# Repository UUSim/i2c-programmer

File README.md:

# Handheld i2c bus programmer (with real time clock)
This repository hosts the Kicad-based design for a handheld i2c bus programmer/scanner with real time clock. The device features:
- DC power (rated 7-12V)
- Powered via i2c bus connector (TBD)
- LCD user interface
- Input via rotary encoder with switch
- It's own clock (on separate i2c bus) + battery backup
- Configurable i2c pullup resistors
- Square wave signal of DS1307 accessible via header

Functions:
- Scan for devices on i2c bus
- Debug i2c protocol
- Set/Read time of internal RTC
- Set/Read time RTC on external i2c bus
- Expose own RTC to external i2c bus
- Communicate with i2c devices on bus

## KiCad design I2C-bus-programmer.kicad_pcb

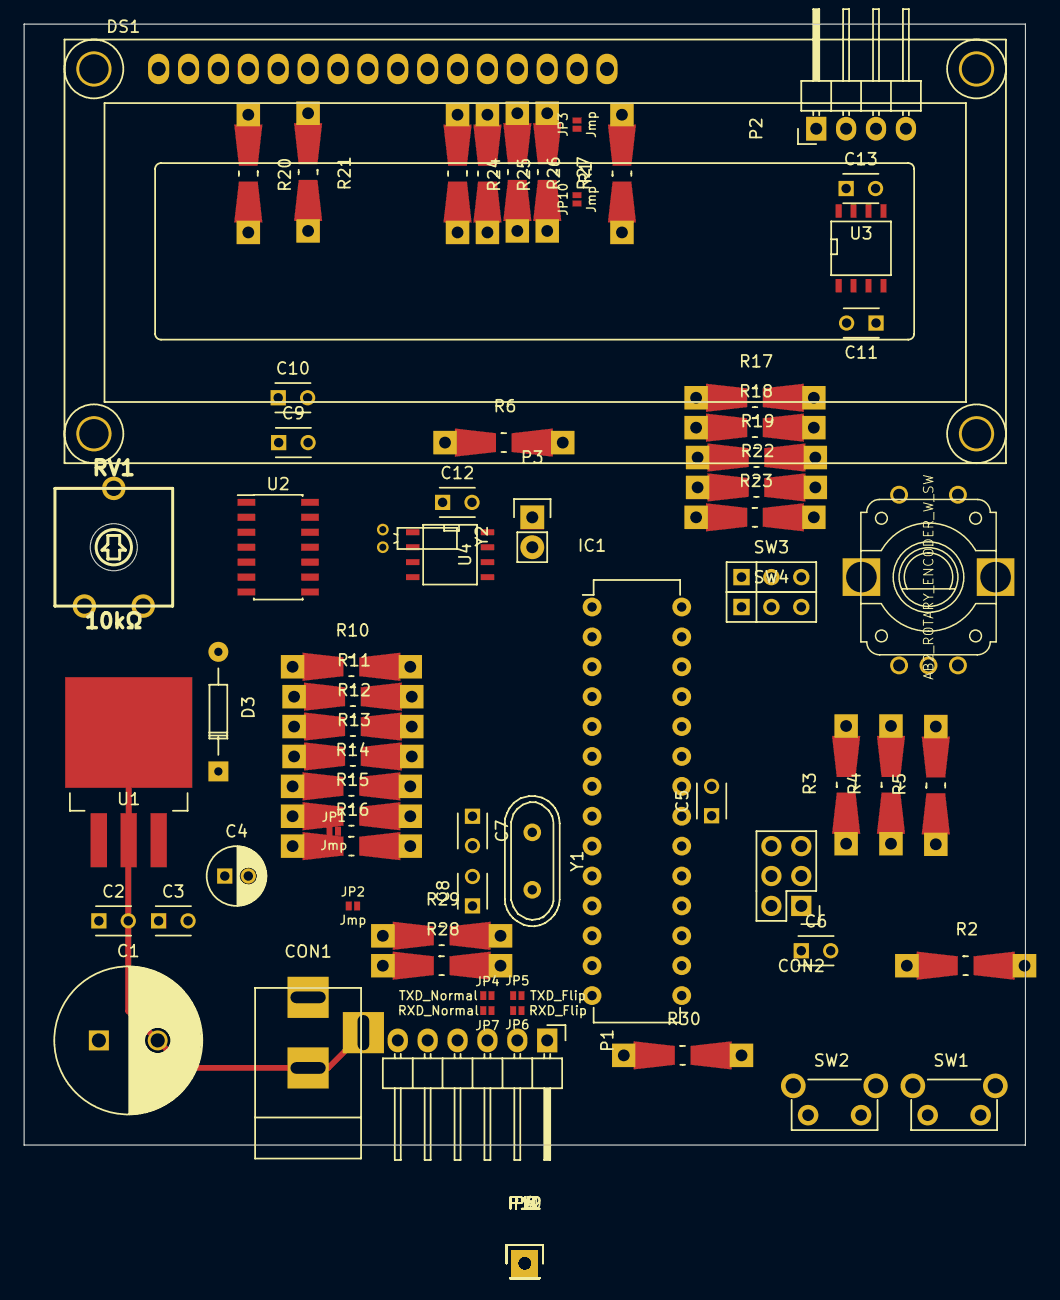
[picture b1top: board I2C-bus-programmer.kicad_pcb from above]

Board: 2 copper layers, 85.1 x 95.2 mm, 77 parts (0 on the bottom side), 61 nets.

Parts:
C1: 2200μF; C_Radial_D12.5_L25_P5
C2, C3, C5, C9, C12: 0.1μF; C_Disc_D3_P2.5
C4: 10μF; C_Radial_D5_L11_P2
C6: 100nF; C_Disc_D3_P2.5
C7, C8: 22pF; C_Disc_D3_P2.5
C10, C11, C13: 1μF; C_Disc_D3_P2.5
CON1: BARREL_JACK
CON2: AVR-ISP-6; Pin_Header_Straight_2x03
D3: 1N4148; Diode_DO-35_SOD27_Horizontal_RM10
DS1: LCD16X2; WC1602A
IC1: ATMEGA328P-P; DIP-28_W7.62mm
JP1, JP2, JP3, JP10: Jmp; S_JUMPER_2
JP4: TXD_Normal; S_JUMPER_2
JP5: TXD_Flip; S_JUMPER_2
JP6: RXD_Flip; S_JUMPER_2
JP7: RXD_Normal; S_JUMPER_2
P1: FTDI_Header; Pin_Header_Angled_1x06
P2: I2C_Header; Pin_Header_Angled_1x04
P3: CONN_01X02; Pin_Header_Straight_1x02
P4, P5, P6, P7, P8, P9, P10, P11, P12: CONN_01X01; Pin_Header_Straight_1x01
R1: 220Ω; Resistor_SMD+THTuniversal_0805to1206_RM10_HandSoldering
R2, R3, R4, R5, R6, R10, R11, R12, R13, R30: 10kΩ; Resistor_SMD+THTuniversal_0805to1206_RM10_HandSoldering
R14, R15, R16, R17, R18, R19, R22, R23: 4.7kΩ; Resistor_SMD+THTuniversal_0805to1206_RM10_HandSoldering
R20, R21, R24, R25, R26, R27, R28, R29: 100Ω; Resistor_SMD+THTuniversal_0805to1206_RM10_HandSoldering
ROT_ENC1: AB2_ROTARY_ENCODER_W_SW; AB2_ROTARY_ENCODER_W_SWITCH
RV1: 10kΩ; trimmer_ecp_ca9-v10
SW1, SW2: SW_Push; SW_Tactile_SPST_Angled
SW3, SW4: SW_SPDT; SW_Micro_SPST
U1: LM7805CT; TO-263-3Lead
U2: PCA9543; SOIC-14_3.9x8.7mm_Pitch1.27mm
U3: ISO1540; SOIC-8-N
U4: DS1307Z+; SOIC-8-N
Y1: 16MHz; Crystal_HC49-U_Vertical
Y2: 32.768kHz; Crystal_Round_Horizontal_2mm

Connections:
+5V: C9.1, C10.1, C11.2, C12.2, CON2.2, DS1.2, IC1.7, IC1.20, JP2.2, JP3.2, P1.4, P11.1, R1.2, R2.1, R3.1, R4.1, R5.1, R6.1, R10.2, R11.2, R12.2, R13.2, R14.1, R15.1, R16.1, R17.1, R18.1, R19.1, R30.1, RV1.1, U2.14, U3.1, U4.8
+12V: C1.1, C2.1, CON1.1, D3.1, U1.1
/DTR: C6.2, P1.1
/RXI: JP5.2, JP7.2, P1.3
/TXO: JP4.2, JP6.2, P1.2
Button1: IC1.26, SW2.1
CLK: CON2.3, IC1.19, R27.2
GNDA: C5.2, C7.2, C8.2, C9.2, C10.2, C11.1, C12.1, CON2.6, DS1.1, DS1.5, DS1.16, IC1.8, IC1.22, JP1.2, P1.5, P1.6, P3.2, P12.1, R30.2, ROT_ENC1.2, ROT_ENC1.6, RV1.3, SW1.2, SW2.2, U2.1, U2.2, U2.7, U3.4, U4.4
GNDPWR: C1.2, C2.2, C3.2, C4.2, CON1.2, CON1.3, JP1.1, U1.2
GND_Iso: C13.2, P2.3, U3.5
Lcd_D4: IC1.14, R24.2
Lcd_D5: IC1.15, R25.2
Lcd_D6: IC1.16, R26.2
Lcd_E: CON2.4, IC1.17, R21.2
Lcd_RS: CON2.1, IC1.18, R20.2
unnamed: C3.1, C4.1, D3.2, JP2.1, U1.3
unnamed: C5.1, IC1.21
unnamed: DS1.3, RV1.2
unnamed: DS1.4, R20.1
unnamed: DS1.6, R21.1
unnamed: DS1.11, R24.1
unnamed: DS1.12, R25.1
unnamed: DS1.13, R26.1
unnamed: DS1.14, R27.1
unnamed: DS1.15, JP3.1, JP10.2
unnamed: JP4.1, JP5.1, R28.1
unnamed: JP6.1, JP7.1, R29.1
unnamed: JP10.1, R1.1
unnamed: P3.1, R6.2, U4.7
unnamed: P4.1, SW3.3
unnamed: P5.1, SW4.3
unnamed: R11.1, U2.4
unnamed: R12.1, U2.8
unnamed: R13.1, U2.11
unnamed: R22.2, SW3.1
unnamed: R23.2, SW4.1
unnamed: U4.1, Y2.1
unnamed: U4.2, Y2.2
Pin_PC1: IC1.24, P6.1
Pin_PD2: IC1.4, P7.1
Pin_PD4: IC1.6, P8.1
Pin_PD5: IC1.11, P9.1
Pin_PD6: IC1.12, P10.1
RXD: IC1.2, R29.2
Reset: C6.1, CON2.5, IC1.1, R2.2, SW1.1
RotEnc1: IC1.5, R4.2, ROT_ENC1.1
RotEnc2: IC1.25, R5.2, ROT_ENC1.3
Rot_Button: IC1.23, R3.2, ROT_ENC1.4
SCL: IC1.28, R15.2, U2.12
SCL_Ext: R17.2, U2.6, U3.3
SCL_Iso: P2.4, SW4.2, U3.6
SCL_Rtc: R19.2, U2.10, U4.6
SDA: IC1.27, R14.2, U2.13
SDA_Ext: R16.2, U2.5, U3.2
SDA_Iso: P2.2, SW3.2, U3.7
SDA_Rtc: R18.2, U2.9, U4.5
TXD: IC1.3, R28.2
VCC_Iso: C13.1, P2.1, R22.1, R23.1, U3.8
XTAL1: C7.1, IC1.9, Y1.1
XTAL2: C8.1, IC1.10, Y1.2
i2c_reset: IC1.13, R10.1, U2.3

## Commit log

2017-01-16 Added screenshot of schematic
2017-01-16 Added project description to readme
2017-01-16 Initial upload of KiCad project files
    The PCB is not yet routed. Components are placed preliminary.
2017-01-29 Added USB interface to schematic
    Added a B-type usb connector for providing a serial interface to the programmer
2017-01-29 Updated schematic info and screenshot.
2017-01-30 Updated USB interface section
    Connected USB interface to different pins, to match pins used for
    v-usb. Added USB D- 2.2k pullup to atmega pin to enable USB
    connects/disconnects through software. Moved 1 pin of the rotary
    encoder onto the INT1 pin.
2017-02-05 Completed wiring for PCA9543 i2c bus switch. Added i2c pull-up resistors.
    Wired reset pin of PCA9543 and added required pull-ups to interrupt
    pins. Added pull-ups to internal i2c busses. Added switchable pull-ups
    to isolated i2c bus.
2017-02-06 Added ISP header. Added protection resistors for mcu pins.
    Also added flyback diode for power regulator for when powered via usb.
2017-11-22 Reduced feature creep
    Removed USB connector and circuitry.
    Added proto-pads for unused MCU pins.
2017-11-22 Updated readme after removal of USB connector.
